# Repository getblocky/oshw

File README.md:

# oshw
Open source hardware designs for Blocky.

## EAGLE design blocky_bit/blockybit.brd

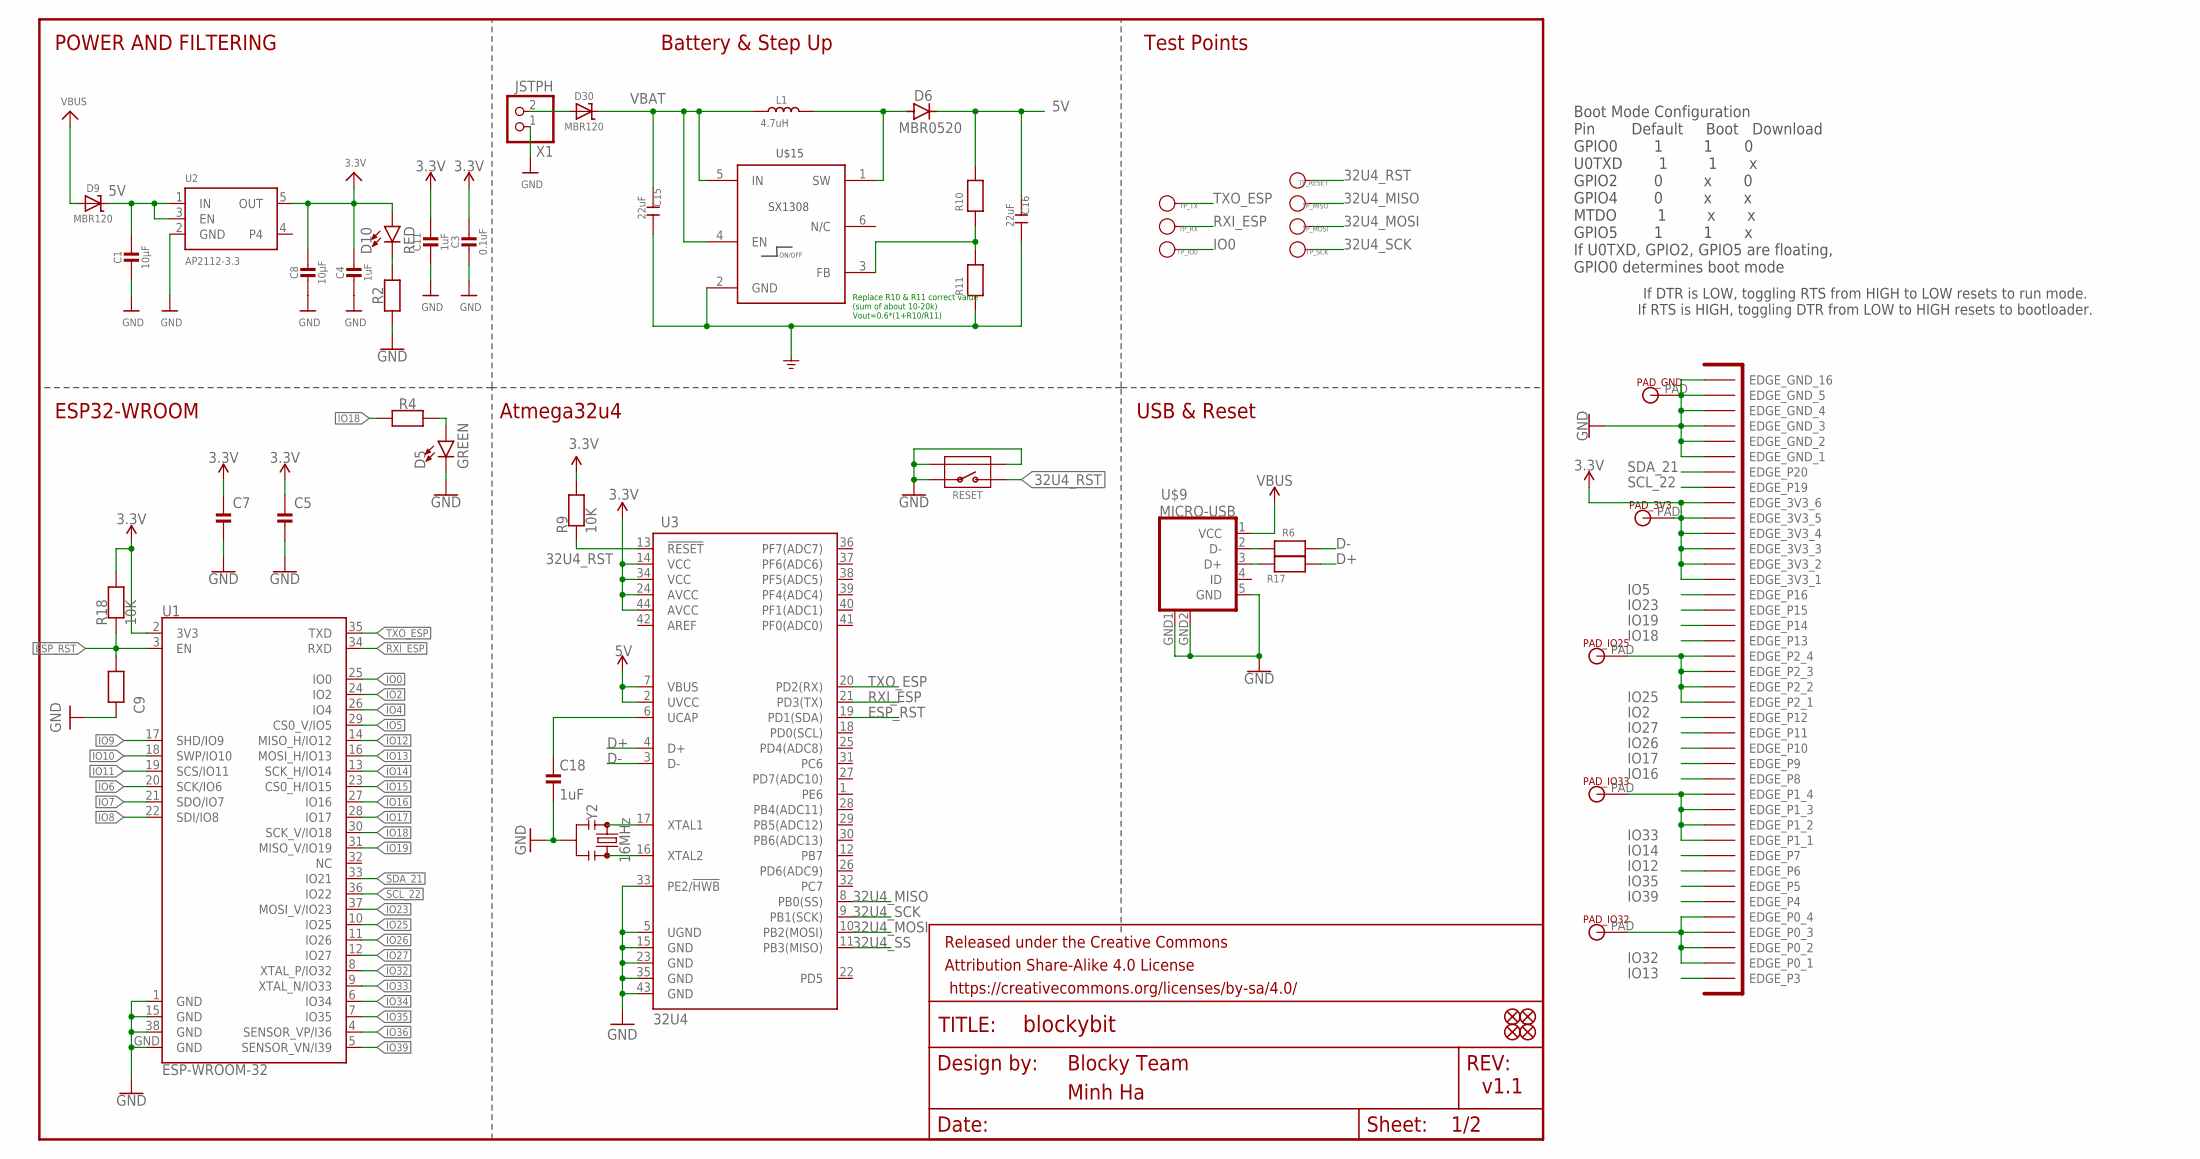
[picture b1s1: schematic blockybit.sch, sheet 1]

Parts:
C1, C8: 10µF; _0603
C3, C7, C9: 0.1uF; _0603
C4, C11, C18: 1uF; _0603
C5: 10uF; _0603
C15, C16: 22uF; C0805
D5: GREEN; LED-0603
D6: MBR0520; SOD123
D9, D30: MBR120; SOD-123
D10: RED; LED-0603
FD1, FD2, FD3, FD4: FIDUCIAL1X2; FIDUCIAL-1X2
FRAME1: FRAME-LETTERNO_PACKAGE; DUMMY
L1: 4.7uH; SD32-4R7MC
PAD_3V3: MICROBIT_PADMICROBIT_PAD_SMALL; MICROBIT_PAD_SMALL
PAD_GND: MICROBIT_PADMICROBIT_PAD_SMALL; MICROBIT_PAD_SMALL
PAD_IO25, PAD_IO32, PAD_IO33: MICROBIT_PADMICROBIT_PAD_SMALL; MICROBIT_PAD_SMALL
R2, R4: 1k; _0603
R6, R17: 22R; _0603
R9, R18: 10K; _0603
R10: 13K; _0603
R11: 2K; _0603
RESET: BUTTON-4P-REINFORCE'TS-1188E'; 4P-SMD-7X3.5X3.5H
TP_IO0: PAD-TEST-POINT'3535'; TP_3535
TP_MISO: PAD-TEST-POINT'3535'; TP_3535
TP_MOSI: PAD-TEST-POINT'3535'; TP_3535
TP_RESET: PAD-TEST-POINT'3535'; TP_3535
TP_RX: PAD-TEST-POINT'3535'; TP_3535
TP_SCK: PAD-TEST-POINT'3535'; TP_3535
TP_TX: PAD-TEST-POINT'3535'; TP_3535
U1: ESP-WROOM-32
U2: AP2112-3.3; SOT23-5
U3: 32U4; QFN-44
U$1: BBC_EDGE
U$9: MICRO-USB
U$15: SX1308; SOT-23-6
X1: JSTPH; JSTPH2
Y2: 16MHz; RESONATOR-SMD-3.2X1.3

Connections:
3.3V: C3.1, C4.1, C5.1, C7.1, C8.1, C11.1, D10.A, PAD_3V3.PAD, R9.2, R18.2, U1.2 (3V3), U2.5 (OUT), U3.14 (VCC), U3.24 (AVCC), U3.34 (VCC), U3.44 (AVCC), U$1.P$67 (EDGE_3V3_1), U$1.P$68 (EDGE_3V3_2), U$1.P$69 (EDGE_3V3_3), U$1.P$70 (EDGE_3V3_4), U$1.P$71 (EDGE_3V3_5), U$1.P$72 (EDGE_3V3_6); also elsewhere on the board
5V: C1.1, C16.1, D6.C, D9.C, R10.2, U2.1 (IN), U2.3 (EN), U3.2 (UVCC), U3.7 (VBUS); also elsewhere on the board
32U4_MISO: TP_MISO.T, U3.8 (PB0(SS))
32U4_MOSI: TP_MOSI.T, U3.10 (PB2(MOSI))
32U4_RST: R9.1, RESET.2, TP_RESET.T, U3.13 (!RESET)
32U4_SCK: TP_SCK.T, U3.9 (PB1(SCK))
32U4_SS: U3.11 (PB3(MISO))
D+: R17.1, U3.4 (D+)
D-: R6.1, U3.3 (D-)
ESP_RST: C9.1, R18.1, U1.3 (EN), U3.19 (PD1(SDA))
FB1: R10.1, R11.2, U$15.3 (FB)
GND: C1.2, C3.2, C4.2, C5.2, C7.2, C8.2, C9.2, C11.2, C15.2, C16.2, C18.1, D5.C, PAD_GND.PAD, R2.1, R11.1, RESET.1, RESET.S1, RESET.S2, U1.1 (GND), U1.15 (GND), U1.38 (GND), U1.GND, U2.2 (GND), U3.5 (UGND), U3.15 (GND), U3.23 (GND), U3.33 (PE2/!HWB), U3.35 (GND), U3.43 (GND), U$1.P$75 (EDGE_GND_1), U$1.P$76 (EDGE_GND_2), U$1.P$77 (EDGE_GND_3), U$1.P$78 (EDGE_GND_4), U$1.P$79 (EDGE_GND_5), U$1.P$80 (EDGE_GND_16), U$9.5 (GND), U$9.GND1 (GND), U$9.GND2 (GND), U$15.2 (GND), X1.1, Y2.2; also elsewhere on the board
IO0: TP_IO0.T, U1.25 (IO0)
IO2: U1.24 (IO2), U$1.P$58 (EDGE_P12)
IO4: U1.26 (IO4); also elsewhere on the board
IO5: U1.29 (CS0_V/IO5), U$1.P$66 (EDGE_P16)
IO6: U1.20 (SCK/IO6)
IO7: U1.21 (SDO/IO7)
IO8: U1.22 (SDI/IO8)
IO9: U1.17 (SHD/IO9)
IO10: U1.18 (SWP/IO10)
IO11: U1.19 (SCS/IO11)
IO12: U1.14 (MISO_H/IO12), U$1.P$48 (EDGE_P6)
IO13: U1.16 (MOSI_H/IO13), U$1.P$41 (EDGE_P3)
IO14: U1.13 (SCK_H/IO14), U$1.P$49 (EDGE_P7)
IO15: U1.23 (CS0_H/IO15)
IO16: U1.27 (IO16), U$1.P$54 (EDGE_P8)
IO17: U1.28 (IO17), U$1.P$55 (EDGE_P9)
IO18: R4.1, U1.30 (SCK_V/IO18), U$1.P$63 (EDGE_P13)
IO19: U1.31 (MISO_V/IO19), U$1.P$64 (EDGE_P14)
IO23: U1.37 (MOSI_V/IO23), U$1.P$65 (EDGE_P15)
IO25: PAD_IO25.PAD, U1.10 (IO25), U$1.P$59 (EDGE_P2_1), U$1.P$60 (EDGE_P2_2), U$1.P$61 (EDGE_P2_3), U$1.P$62 (EDGE_P2_4); also elsewhere on the board
IO26: U1.11 (IO26), U$1.P$56 (EDGE_P10)
IO27: U1.12 (IO27), U$1.P$57 (EDGE_P11); also elsewhere on the board
IO32: PAD_IO32.PAD, U1.8 (XTAL_P/IO32), U$1.P$42 (EDGE_P0_1), U$1.P$43 (EDGE_P0_2), U$1.P$44 (EDGE_P0_3), U$1.P$45 (EDGE_P0_4)
IO33: PAD_IO33.PAD, U1.9 (XTAL_N/IO33), U$1.P$50 (EDGE_P1_1), U$1.P$51 (EDGE_P1_2), U$1.P$52 (EDGE_P1_3), U$1.P$53 (EDGE_P1_4); also elsewhere on the board
IO34: U1.6 (IO34); also elsewhere on the board
IO35: U1.7 (IO35), U$1.P$47 (EDGE_P5); also elsewhere on the board
IO36: U1.4 (SENSOR_VP/I36); also elsewhere on the board
IO39: U1.5 (SENSOR_VN/I39), U$1.P$46 (EDGE_P4)
unnamed: D30.A, X1.2
unnamed: D5.A, R4.2
unnamed: D10.C, R2.2
unnamed: U3.16 (XTAL2), Y2.3
unnamed: R6.2, U$9.2 (D-)
unnamed: U3.17 (XTAL1), Y2.1
unnamed: R17.2, U$9.3 (D+)
RXI_ESP: TP_RX.T, U1.34 (RXD), U3.21 (PD3(TX))
SCL_22: U1.36 (IO22), U$1.P$73 (EDGE_P19); also elsewhere on the board
SDA_21: U1.33 (IO21), U$1.P$74 (EDGE_P20); also elsewhere on the board
SW1: D6.A, L1.2, U$15.1 (SW)
TXO_ESP: TP_TX.T, U1.35 (TXD), U3.20 (PD2(RX))
UCAP: C18.2, U3.6 (UCAP)
VBAT: C15.1, D30.C, L1.1, U$15.4 (EN), U$15.5 (IN)
VBUS: D9.A, U$9.1 (VCC)

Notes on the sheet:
Boot Mode Configuration Pin Default Boot Download GPIO0 1 1 0 U0TXD 1 1 x GPIO2 0 x 0 GPIO4 0 x x MTDO 1 x x GPIO5 1 1 x If U0TXD, GPIO2, GPIO5 are floating, GPIO0 determines boot mode
If DTR is LOW, toggling RTS from HIGH to LOW resets to run mode. If RTS is HIGH, toggling DTR from LOW to HIGH resets to bootloader.
POWER AND FILTERING
Battery & Step Up
ESP32-WROOM
Atmega32u4
Test Points
Blocky Team
v1.1
Minh Ha
Replace R10 & R11 correct value (sum of about 10-20k) Vout=0.6*(1+R10/R11)
USB & Reset

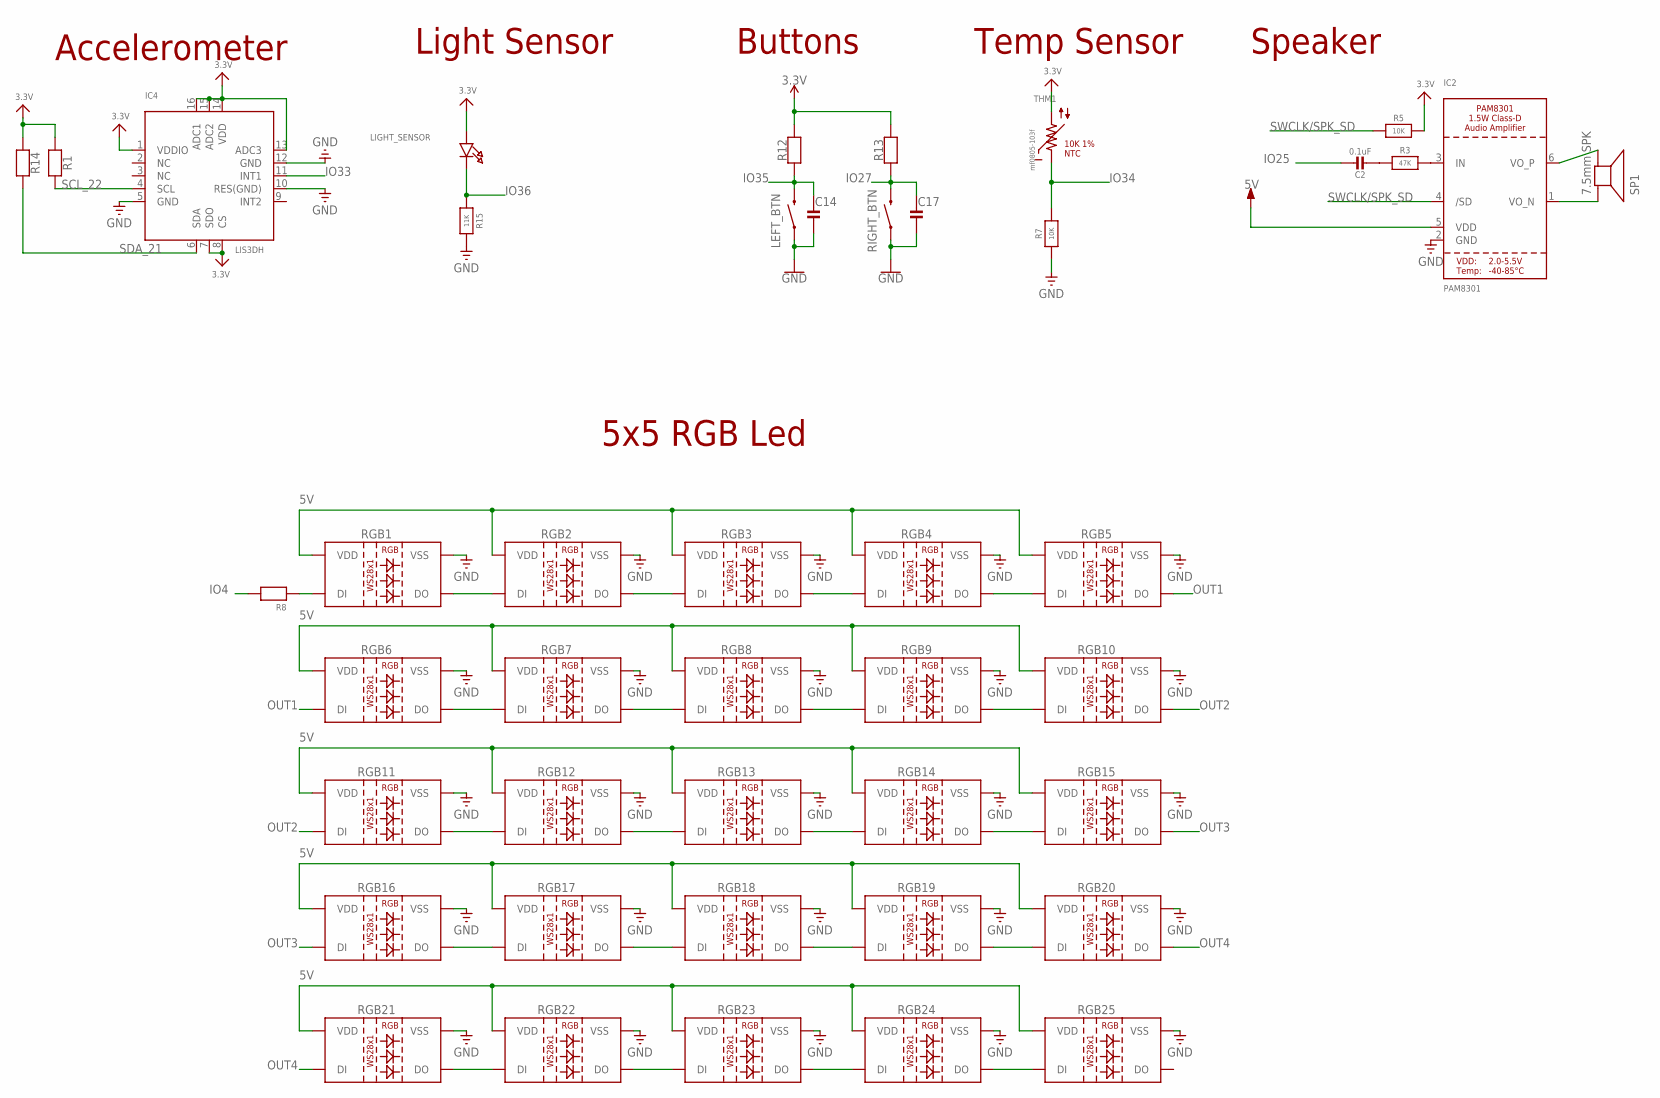
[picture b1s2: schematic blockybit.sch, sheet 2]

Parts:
C2: 0.1uF; _0603
C14, C17: 10pF; _0603
IC2: PAM8301; SOT23-6
IC4: LIS3DH; LGA16_3X3MM
LEFT_BTN: MOMENTARY-SWITCH-SPST-SMD-6.2MM-TALL; TACTILE_SWITCH_SMD_6.2MM_TALL
LIGHT_SENSOR: LED0805; CHIPLED_0805
R1, R5, R7, R12, R13, R14: 10K; _0603
R3: 47K; _0603
R8: 470; _0603
R15: 11K; _0603
RGB1, RGB2, RGB3, RGB4, RGB5, RGB6, RGB7, RGB8, RGB9, RGB10, RGB11, RGB12, RGB13, RGB14, RGB15, RGB16, RGB17, RGB18, RGB19, RGB20, RGB21, RGB22, RGB23, RGB24, RGB25: WS2812B; WS2812B-3535
RIGHT_BTN: MOMENTARY-SWITCH-SPST-SMD-6.2MM-TALL; TACTILE_SWITCH_SMD_6.2MM_TALL
SP1: 7.5mm SPK; BUZZER_SMT_7.5MM
THM1: mf0805-103f; R0805

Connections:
3.3V: IC4.1 (VDDIO), IC4.7 (SDO), IC4.8 (CS), IC4.13 (ADC3), IC4.14 (VDD), IC4.15 (ADC2), IC4.16 (ADC1), LIGHT_SENSOR.A, R1.1, R5.2, R12.2, R13.2, R14.1, THM1.2; also elsewhere on the board
5V: IC2.5 (VDD), RGB1.1 (VDD), RGB2.1 (VDD), RGB3.1 (VDD), RGB4.1 (VDD), RGB5.1 (VDD), RGB6.1 (VDD), RGB7.1 (VDD), RGB8.1 (VDD), RGB9.1 (VDD), RGB10.1 (VDD), RGB11.1 (VDD), RGB12.1 (VDD), RGB13.1 (VDD), RGB14.1 (VDD), RGB15.1 (VDD), RGB16.1 (VDD), RGB17.1 (VDD), RGB18.1 (VDD), RGB19.1 (VDD), RGB20.1 (VDD), RGB21.1 (VDD), RGB22.1 (VDD), RGB23.1 (VDD), RGB24.1 (VDD), RGB25.1 (VDD); also elsewhere on the board
GND: C14.2, C17.2, IC2.2 (GND), IC4.5 (GND), IC4.10 (RES(GND)), IC4.12 (GND), LEFT_BTN.A2 (1), R7.1, R15.1, RGB1.3 (VSS), RGB2.3 (VSS), RGB3.3 (VSS), RGB4.3 (VSS), RGB5.3 (VSS), RGB6.3 (VSS), RGB7.3 (VSS), RGB8.3 (VSS), RGB9.3 (VSS), RGB10.3 (VSS), RGB11.3 (VSS), RGB12.3 (VSS), RGB13.3 (VSS), RGB14.3 (VSS), RGB15.3 (VSS), RGB16.3 (VSS), RGB17.3 (VSS), RGB18.3 (VSS), RGB19.3 (VSS), RGB20.3 (VSS), RGB21.3 (VSS), RGB22.3 (VSS), RGB23.3 (VSS), RGB24.3 (VSS), RGB25.3 (VSS), RIGHT_BTN.A2 (1); also elsewhere on the board
IO4: R8.2; also elsewhere on the board
IO25: C2.1; also elsewhere on the board
IO27: C17.1, R13.1, RIGHT_BTN.B2 (2); also elsewhere on the board
IO33: IC4.11 (INT1); also elsewhere on the board
IO34: R7.2, THM1.1; also elsewhere on the board
IO35: C14.1, LEFT_BTN.B2 (2), R12.1; also elsewhere on the board
IO36: LIGHT_SENSOR.C, R15.2; also elsewhere on the board
unnamed: C2.2, R3.1
unnamed: IC2.3 (IN), R3.2
unnamed: IC2.6 (VO_P), SP1.-
unnamed: IC2.1 (VO_N), SP1.+
unnamed: RGB1.2 (DO), RGB2.4 (DI)
unnamed: RGB2.2 (DO), RGB3.4 (DI)
unnamed: RGB3.2 (DO), RGB4.4 (DI)
unnamed: RGB4.2 (DO), RGB5.4 (DI)
unnamed: RGB6.2 (DO), RGB7.4 (DI)
unnamed: RGB7.2 (DO), RGB8.4 (DI)
unnamed: R8.1, RGB1.4 (DI)
unnamed: RGB8.2 (DO), RGB9.4 (DI)
unnamed: RGB9.2 (DO), RGB10.4 (DI)
unnamed: RGB11.2 (DO), RGB12.4 (DI)
unnamed: RGB12.2 (DO), RGB13.4 (DI)
unnamed: RGB13.2 (DO), RGB14.4 (DI)
unnamed: RGB14.2 (DO), RGB15.4 (DI)
unnamed: RGB16.2 (DO), RGB17.4 (DI)
unnamed: RGB17.2 (DO), RGB18.4 (DI)
unnamed: RGB18.2 (DO), RGB19.4 (DI)
unnamed: RGB19.2 (DO), RGB20.4 (DI)
unnamed: RGB21.2 (DO), RGB22.4 (DI)
unnamed: RGB22.2 (DO), RGB23.4 (DI)
unnamed: RGB23.2 (DO), RGB24.4 (DI)
unnamed: RGB24.2 (DO), RGB25.4 (DI)
OUT1: RGB5.2 (DO), RGB6.4 (DI)
OUT2: RGB10.2 (DO), RGB11.4 (DI)
OUT3: RGB15.2 (DO), RGB16.4 (DI)
OUT4: RGB20.2 (DO), RGB21.4 (DI)
SCL_22: IC4.4 (SCL), R1.2; also elsewhere on the board
SDA_21: IC4.6 (SDA), R14.2; also elsewhere on the board
SWCLK/SPK_SD: IC2.4 (/SD), R5.1

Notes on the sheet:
Accelerometer
Light Sensor
Buttons
10K 1% NTC
Temp Sensor
Speaker
5x5 RGB Led

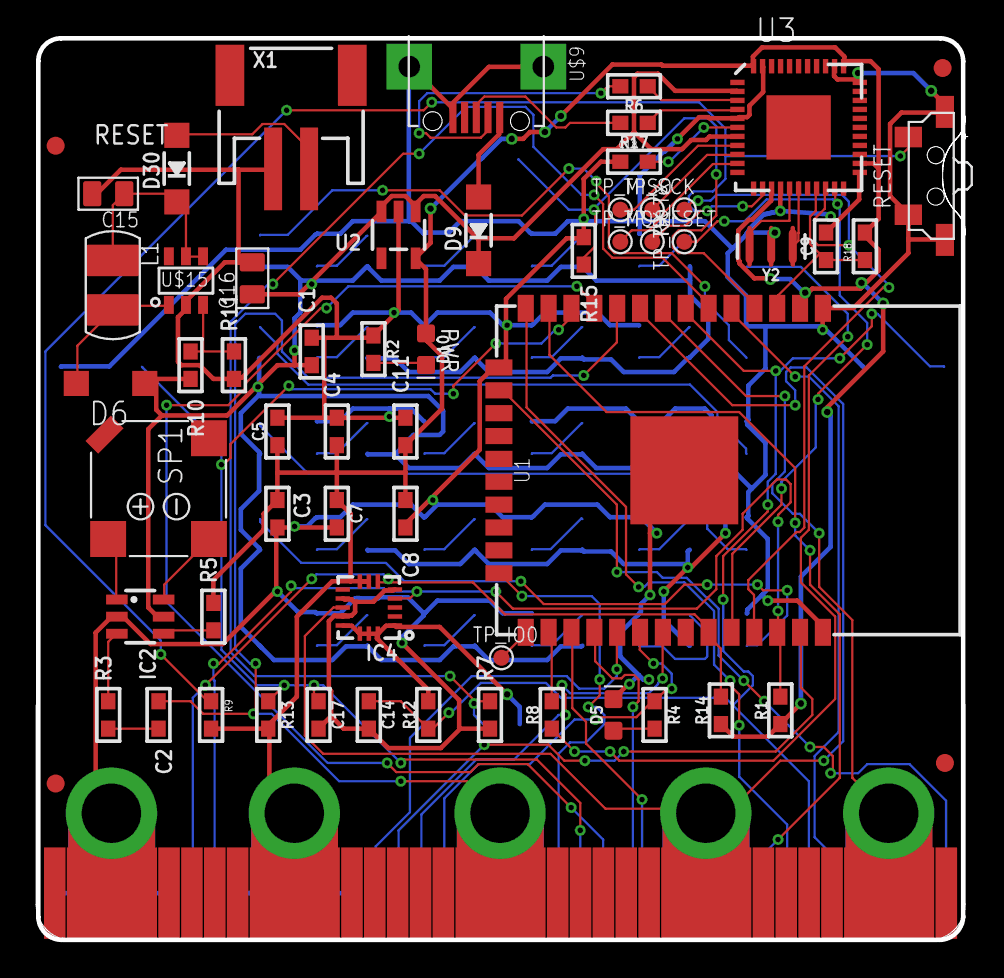
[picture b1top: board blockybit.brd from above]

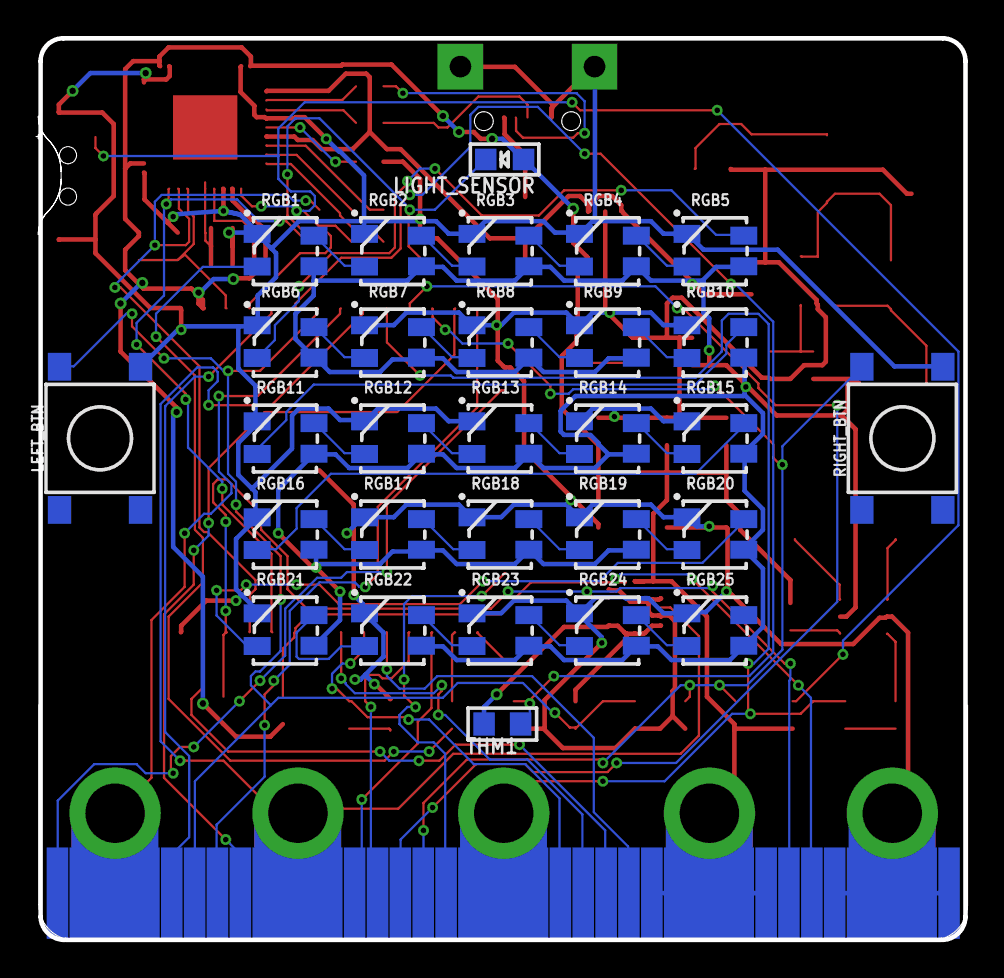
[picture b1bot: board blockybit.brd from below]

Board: 2 copper layers, 51.5 x 50.1 mm, 95 parts (29 on the bottom side), 77 nets.

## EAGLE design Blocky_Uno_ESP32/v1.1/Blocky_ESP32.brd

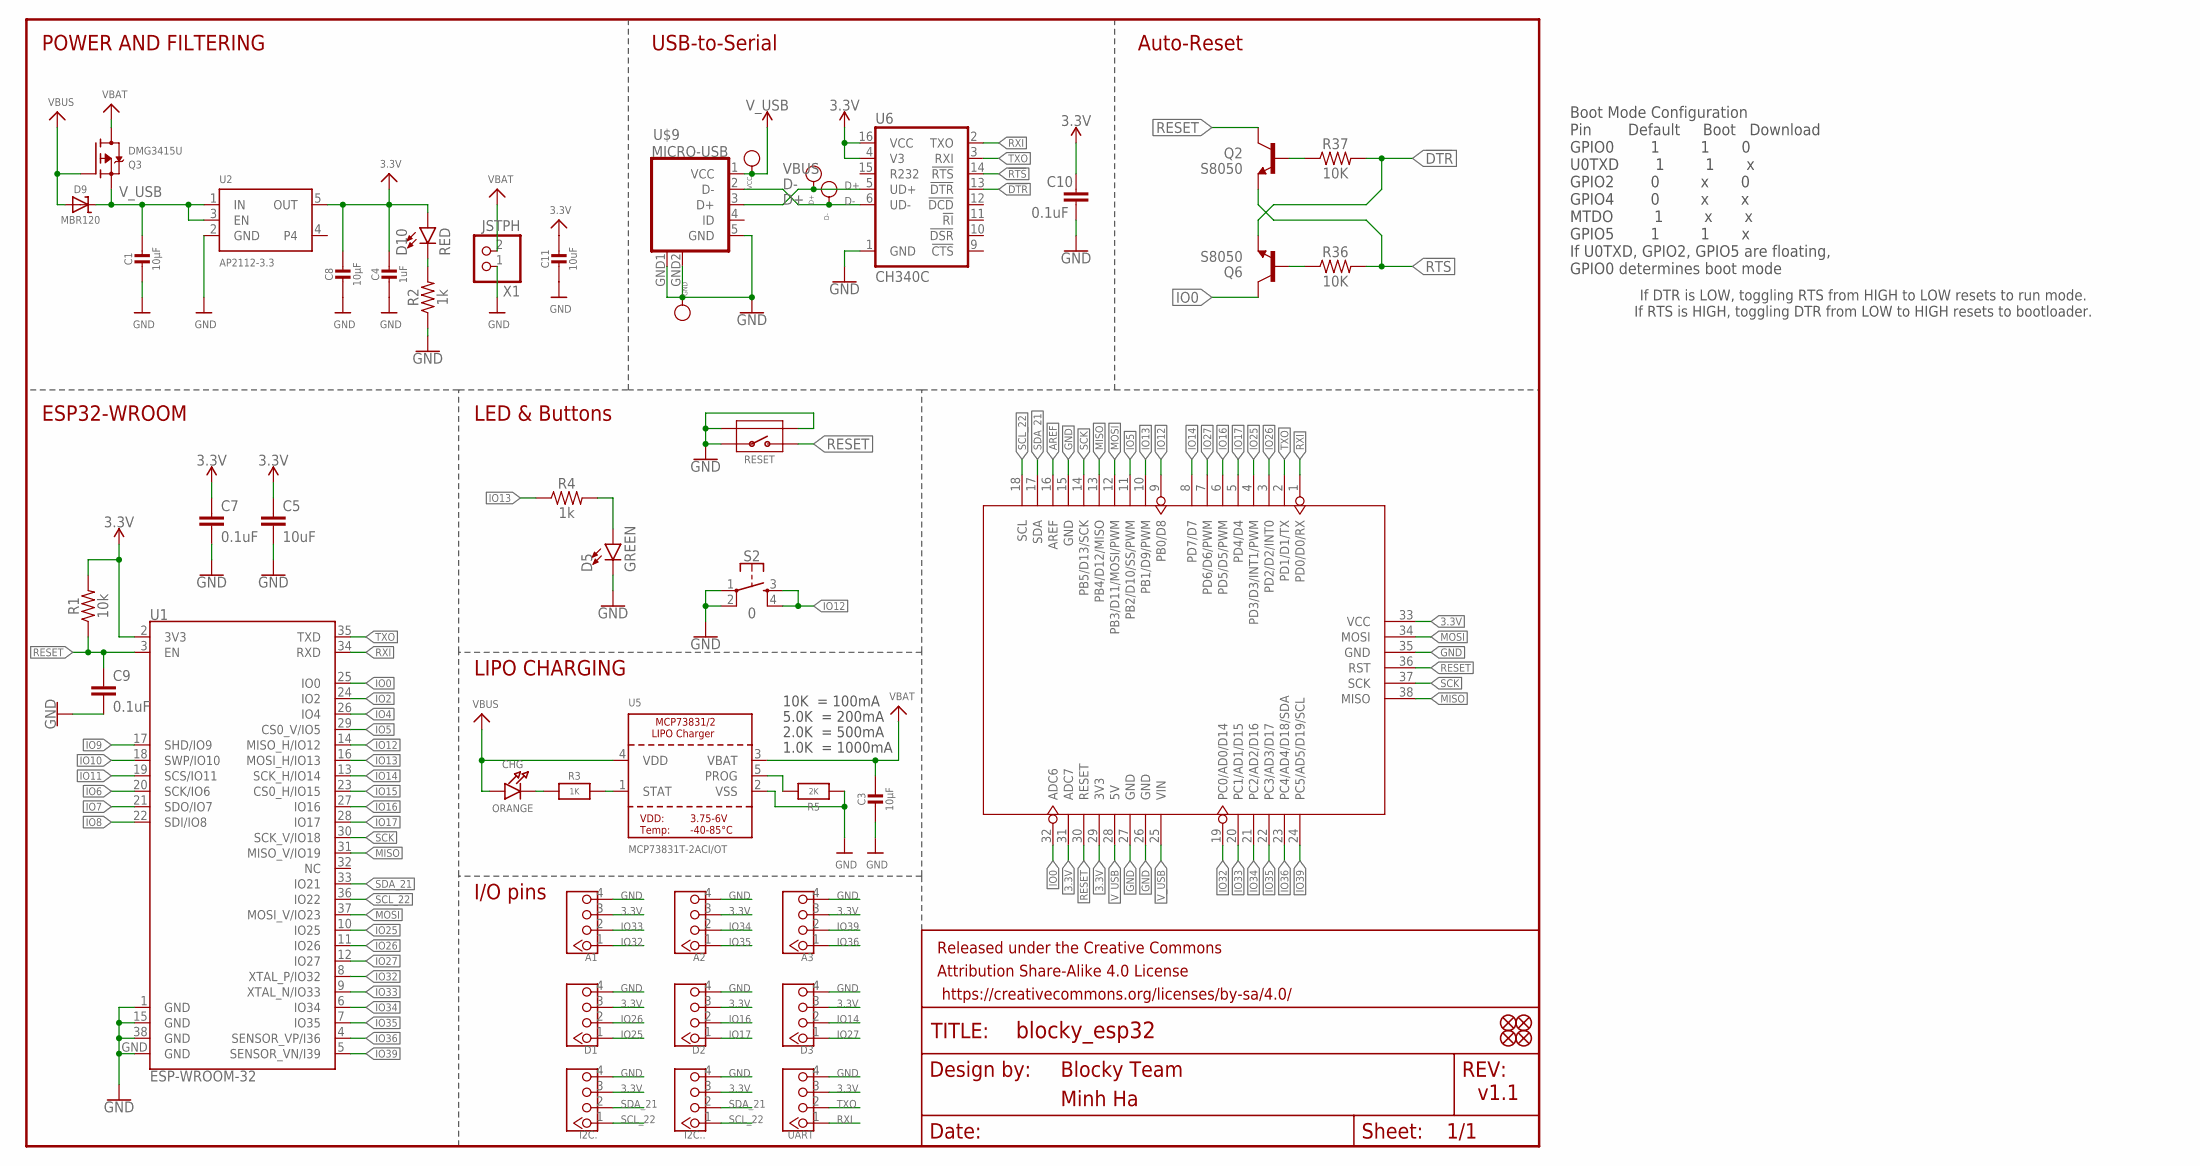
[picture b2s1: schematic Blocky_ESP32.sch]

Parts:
A1, A2, A3: TWIG-4P-2.0-2.0; 4P-2.0
C1, C3, C8: 10µF; _0603
C4: 1uF; _0603
C5: 10uF; 0603
C7, C9, C10: 0.1uF; 0603
C11: 10uF; _0603
CHG: ORANGE; CHIPLED_0603
D1, D2, D3: TWIG-4P-2.0-2.0; 4P-2.0
D5: GREEN; LED-0603
D9: MBR120; SOD-123
D10: RED; LED-0603
D+: PAD-TEST-POINT'4545'; TP_4545
D-: PAD-TEST-POINT'4545'; TP_4545
FD1, FD2, FD3, FD4: FIDUCIAL1X2; FIDUCIAL-1X2
FRAME1: FRAME-LETTERNO_PACKAGE; DUMMY
GND: PAD-TEST-POINT'4545'; TP_4545
I2C., I2C..: TWIG-4P-2.0-2.0; 4P-2.0
Q2, Q6: S8050; SOT23-3
Q3: DMG3415U; SOT23-R
R1: 10k; 0603
R2, R4: 1k; 0603
R3: 1K; 0603-NO
R5: 2K; 0603-NO
R36, R37: 10K; 0603
RESET: BUTTON-4P-REINFORCE'TS-1188E'; 4P-SMD-7X3.5X3.5H
S2: 0; TACTILE_SWITCH_SMD_4.6X2.8MM
U1: ESP-WROOM-32
U2: AP2112-3.3; SOT23-5
U3: ARDUINO-38P
U5: MCP73831T-2ACI/OT; SOT23-5
U6: CH340C; SO016
U$9: MICRO-USB
UART: TWIG-4P-2.0-2.0; 4P-2.0
VCC: PAD-TEST-POINT'4545'; TP_4545
X1: JSTPH; JSTPH2

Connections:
3.3V: A1.3, A2.3, A3.3, C4.1, C5.1, C7.1, C8.1, C10.1, C11.1, D1.3, D2.3, D3.3, D10.A, I2C..3, I2C...3, R1.2, U1.2 (3V3), U2.5 (OUT), U3.29 (3V3), U3.31 (ADC7), U3.33 (VCC), U6.4 (V3), U6.16 (VCC), UART.3
!DTR: Q6.2 (E), R37.2, U6.13 (!DTR)
!RTS: Q2.2 (E), R36.2, U6.14 (!RTS)
AREF: U3.16 (AREF)
D+: D+.T, U6.5 (UD+), U$9.3 (D+)
D-: D-.T, U6.6 (UD-), U$9.2 (D-)
GND: A1.4, A2.4, A3.4, C1.2, C3.2, C4.2, C5.2, C7.2, C8.2, C9.2, C10.2, C11.2, D1.4, D2.4, D3.4, D5.C, GND.T, I2C..4, I2C...4, R2.1, R5.1, RESET.1, RESET.S1, RESET.S2, S2.1, S2.2, U1.1 (GND), U1.15 (GND), U1.38 (GND), U1.GND, U2.2 (GND), U3.15 (GND), U3.26 (GND), U3.27 (GND), U3.35 (GND), U5.2 (VSS), U6.1 (GND), U$9.5 (GND), U$9.GND1 (GND), U$9.GND2 (GND), UART.4, X1.1
IO0: Q6.3 (C), U1.25 (IO0), U3.32 (ADC6)
IO2: U1.24 (IO2)
IO4: U1.26 (IO4)
IO5: U1.29 (CS0_V/IO5), U3.11 (PB2/D10/SS/PWM)
IO6: U1.20 (SCK/IO6)
IO7: U1.21 (SDO/IO7)
IO8: U1.22 (SDI/IO8)
IO9: U1.17 (SHD/IO9)
IO10: U1.18 (SWP/IO10)
IO11: U1.19 (SCS/IO11)
IO12: S2.3, S2.4, U1.14 (MISO_H/IO12), U3.9 (PB0/D8)
IO13: R4.1, U1.16 (MOSI_H/IO13), U3.10 (PB1/D9/PWM)
IO14: D3.2, U1.13 (SCK_H/IO14), U3.8 (PD7/D7)
IO15: U1.23 (CS0_H/IO15)
IO16: D2.2, U1.27 (IO16), U3.6 (PD5/D5/PWM)
IO17: D2.1, U1.28 (IO17), U3.5 (PD4/D4)
IO25: D1.1, U1.10 (IO25), U3.4 (PD3/D3/INT1/PWM)
IO26: D1.2, U1.11 (IO26), U3.3 (PD2/D2/INT0)
IO27: D3.1, U1.12 (IO27), U3.7 (PD6/D6/PWM)
IO32: A1.1, U1.8 (XTAL_P/IO32), U3.19 (PC0/AD0/D14)
IO33: A1.2, U1.9 (XTAL_N/IO33), U3.20 (PC1/AD1/D15)
IO34: A2.2, U1.6 (IO34), U3.21 (PC2/AD2/D16)
IO35: A2.1, U1.7 (IO35), U3.22 (PC3/AD3/D17)
IO36: A3.1, U1.4 (SENSOR_VP/I36), U3.23 (PC4/AD4/D18/SDA)
IO39: A3.2, U1.5 (SENSOR_VN/I39), U3.24 (PC5/AD5/D19/SCL)
MISO: U1.31 (MISO_V/IO19), U3.13 (PB4/D12/MISO), U3.38 (MISO)
MOSI: U1.37 (MOSI_V/IO23), U3.12 (PB3/D11/MOSI/PWM), U3.34 (MOSI)
unnamed: CHG.C, R3.1
unnamed: D5.A, R4.2
unnamed: Q2.1 (B), R37.1
unnamed: D10.C, R2.2
unnamed: Q6.1 (B), R36.1
PROG: R5.2, U5.5 (PROG)
RESET: C9.1, Q2.3 (C), R1.1, RESET.2, U1.3 (EN), U3.30 (RESET), U3.36 (RST)
RXI: U1.34 (RXD), U3.1 (PD0/D0/RX), U6.2 (TXO), UART.1
SCK: U1.30 (SCK_V/IO18), U3.14 (PB5/D13/SCK), U3.37 (SCK)
SCL_22: I2C..1, I2C...1, U1.36 (IO22), U3.18 (SCL)
SDA_21: I2C..2, I2C...2, U1.33 (IO21), U3.17 (SDA)
STAT: R3.2, U5.1 (STAT)
TXO: U1.35 (TXD), U3.2 (PD1/D1/TX), U6.3 (RXI), UART.2
VBAT: C3.1, Q3.3 (D), U5.3 (VBAT), X1.2
VBUS: CHG.A, D9.A, Q3.1 (G), U5.4 (VDD), U$9.1 (VCC), VCC.T
V_USB: C1.1, D9.C, Q3.2 (S), U2.1 (IN), U2.3 (EN), U3.25 (VIN), U3.28 (5V)

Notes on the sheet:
Boot Mode Configuration Pin Default Boot Download GPIO0 1 1 0 U0TXD 1 1 x GPIO2 0 x 0 GPIO4 0 x x MTDO 1 x x GPIO5 1 1 x If U0TXD, GPIO2, GPIO5 are floating, GPIO0 determines boot mode
If DTR is LOW, toggling RTS from HIGH to LOW resets to run mode. If RTS is HIGH, toggling DTR from LOW to HIGH resets to bootloader.
POWER AND FILTERING
USB-to-Serial
I/O pins
ESP32-WROOM
LED & Buttons
Auto-Reset
LIPO CHARGING
Blocky Team
v1.1
Minh Ha
10K = 100mA
5.0K = 200mA
2.0K = 500mA
1.0K = 1000mA

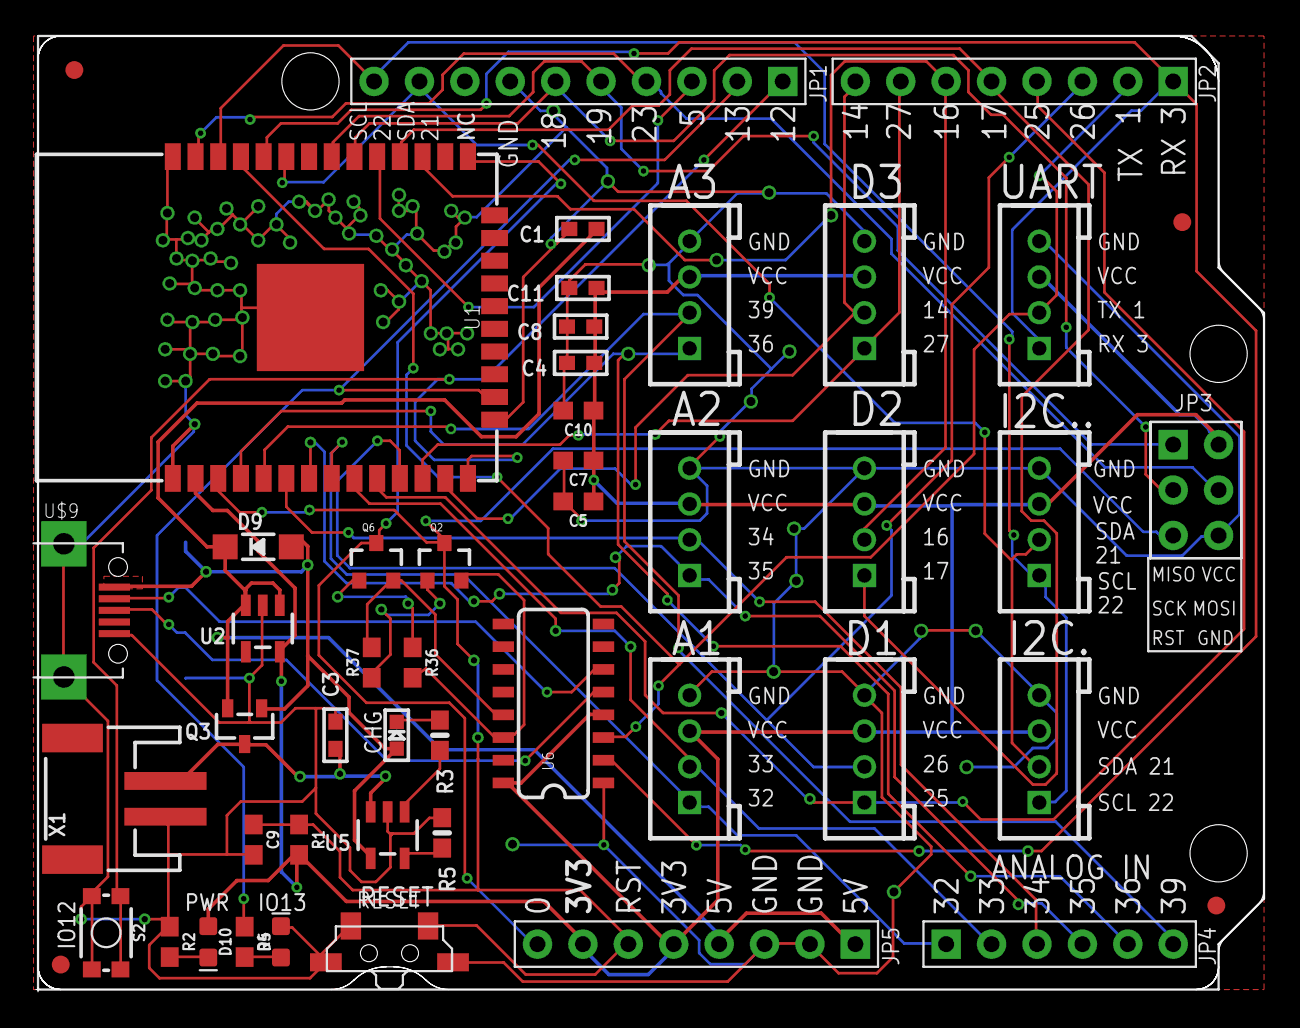
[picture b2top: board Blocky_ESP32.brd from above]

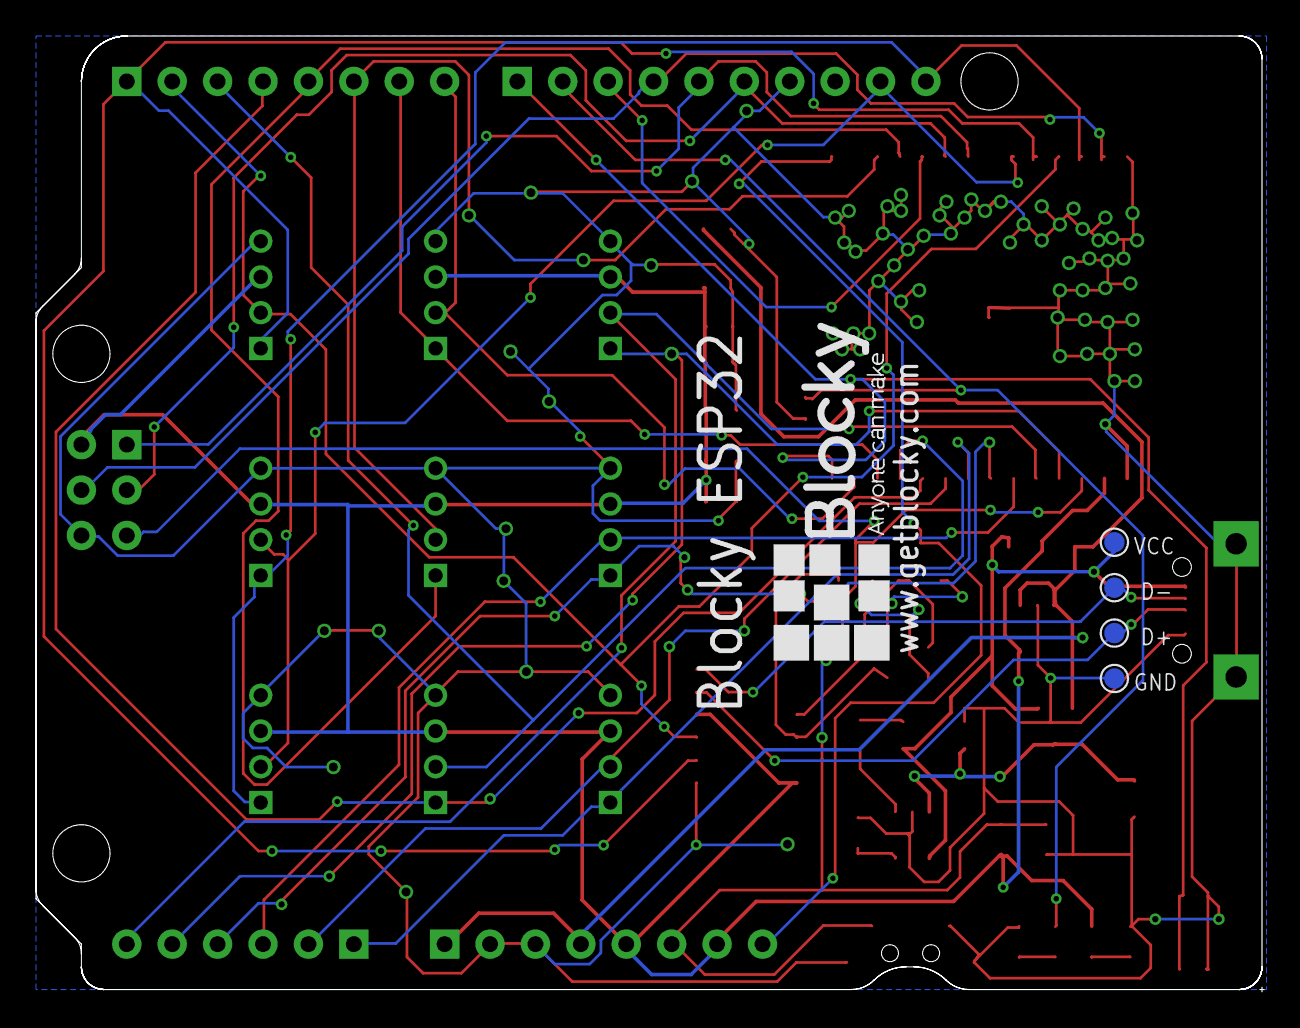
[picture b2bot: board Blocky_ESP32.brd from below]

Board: 2 copper layers, 68.7 x 53.5 mm, 51 parts (5 on the bottom side), 40 nets.

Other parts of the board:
U$4: BLOCKY_LOGO

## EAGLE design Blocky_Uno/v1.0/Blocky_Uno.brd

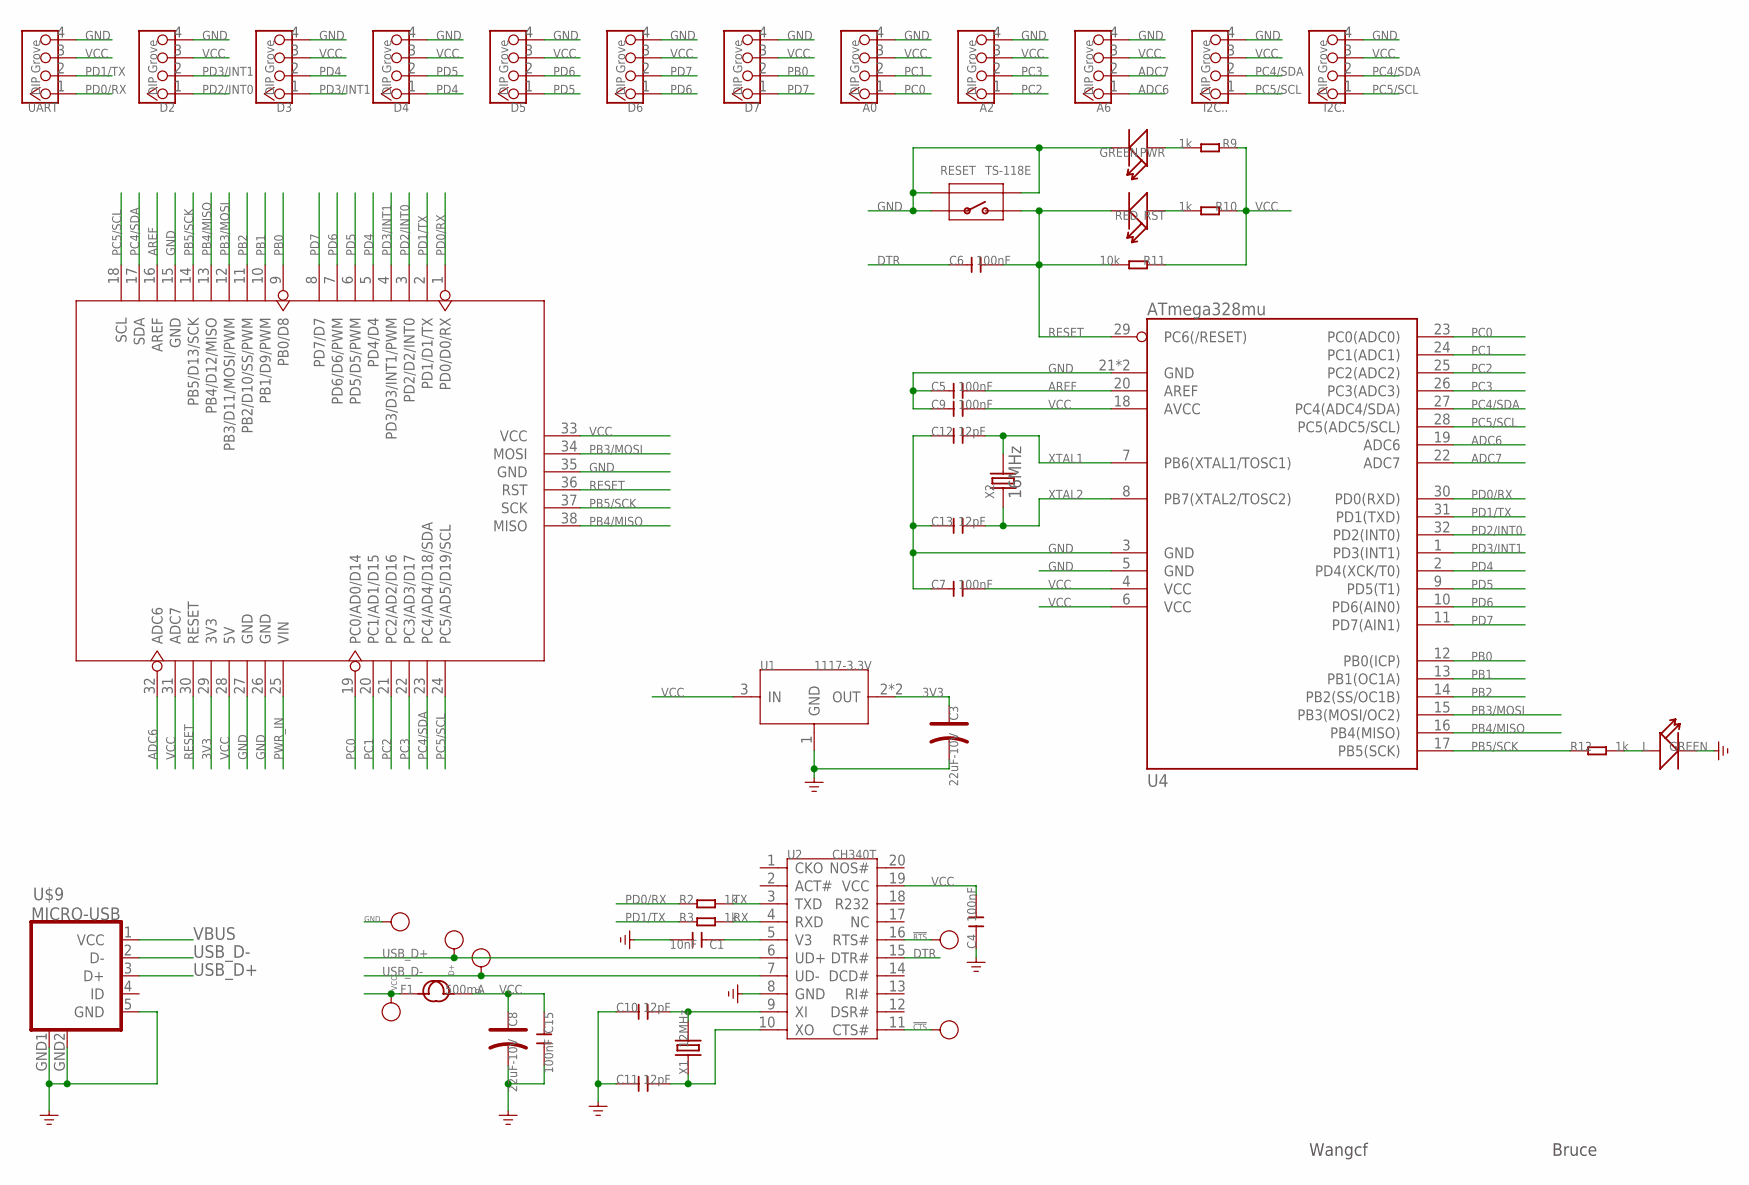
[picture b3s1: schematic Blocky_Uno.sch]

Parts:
!CTS: PAD-TEST-POINT'4545'; TP_4545
!RTS: PAD-TEST-POINT'4545'; TP_4545
A0, A2, A6: DIP Grove; 4P-2.0
C1: 10nF; C0603
C3, C8: 22uF-10V; AVX-A
C4, C5, C6, C7, C9, C15: 100nF; C0603
C10, C11, C12, C13: 12pF; C0603
D2, D3, D4, D5, D6, D7: DIP Grove; 4P-2.0
D+: PAD-TEST-POINT'4545'; TP_4545
D-: PAD-TEST-POINT'4545'; TP_4545
F1: 500mA; F1206
GND: PAD-TEST-POINT'4545'; TP_4545
I2C., I2C..: DIP Grove; 4P-2.0
L: GREEN; LED-0603
PWR: GREEN; LED-0603
R2, R3, R9, R10, R12: 1k; R0603
R11: 10k; R0603
RESET: TS-118E; 4P-SMD-7X3.5X3.5H
RST: RED; LED-0603
U1: 1117-3.3V; SOT89
U2: CH340T; SSOP20
U3: ARDUINO-38P
U4: ATmega328mu; MLF32X-W/HEAT
U$9: MICRO-USB
UART: DIP Grove; 4P-2.0
VCC: PAD-TEST-POINT'4545'; TP_4545
X1: 12MHz; 2P-SMD-5X3.2
X2: 16MHz; 2P-SMD-5X3.2

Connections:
3V3: C3.+, U1.2 (OUT), U1.4 (OUT), U3.29 (3V3)
ADC6: A6.1, U3.32 (ADC6), U4.19 (ADC6)
ADC7: A6.2, U4.22 (ADC7)
AREF: C5.2, U3.16 (AREF), U4.20 (AREF)
CTS: !CTS.T, U2.11 (CTS#)
DTR: C6.1, U2.15 (DTR#)
GND: A0.4, A2.4, A6.4, C1.2, C3.-, C4.1, C5.1, C7.1, C8.-, C9.1, C10.1, C11.1, C12.1, C13.1, C15.2, D2.4, D3.4, D4.4, D5.4, D6.4, D7.4, GND.T, I2C..4, I2C...4, L.-, PWR.-, RESET.1, RESET.S1, RESET.S2, U1.1 (GND), U2.8 (GND), U3.15 (GND), U3.26 (GND), U3.27 (GND), U3.35 (GND), U4.3 (GND), U4.5 (GND), U4.21 (GND), U4.HEAT (GND), U$9.5 (GND), U$9.GND1 (GND), U$9.GND2 (GND), UART.4
unnamed: R10.2, RST.+
unnamed: PWR.+, R9.2
unnamed: C10.2, U2.9 (XI), X1.2
unnamed: C11.2, U2.10 (XO), X1.1
unnamed: !RTS.T, U2.16 (RTS#)
unnamed: L.+, R12.2
PB0: D7.2, U3.9 (PB0/D8), U4.12 (PB0(ICP))
PB1: U3.10 (PB1/D9/PWM), U4.13 (PB1(OC1A))
PB2: U3.11 (PB2/D10/SS/PWM), U4.14 (PB2(SS/OC1B))
PB3/MOSI: U3.12 (PB3/D11/MOSI/PWM), U3.34 (MOSI), U4.15 (PB3(MOSI/OC2))
PB4/MISO: U3.13 (PB4/D12/MISO), U3.38 (MISO), U4.16 (PB4(MISO))
PB5/SCK: R12.1, U3.14 (PB5/D13/SCK), U3.37 (SCK), U4.17 (PB5(SCK))
PC0: A0.1, U3.19 (PC0/AD0/D14), U4.23 (PC0(ADC0))
PC1: A0.2, U3.20 (PC1/AD1/D15), U4.24 (PC1(ADC1))
PC2: A2.1, U3.21 (PC2/AD2/D16), U4.25 (PC2(ADC2))
PC3: A2.2, U3.22 (PC3/AD3/D17), U4.26 (PC3(ADC3))
PC4/SDA: I2C..2, I2C...2, U3.17 (SDA), U3.23 (PC4/AD4/D18/SDA), U4.27 (PC4(ADC4/SDA))
PC5/SCL: I2C..1, I2C...1, U3.18 (SCL), U3.24 (PC5/AD5/D19/SCL), U4.28 (PC5(ADC5/SCL))
PD0/RX: R2.1, U3.1 (PD0/D0/RX), U4.30 (PD0(RXD)), UART.1
PD1/TX: R3.1, U3.2 (PD1/D1/TX), U4.31 (PD1(TXD)), UART.2
PD2/INT0: D2.1, U3.3 (PD2/D2/INT0), U4.32 (PD2(INT0))
PD3/INT1: D2.2, D3.1, U3.4 (PD3/D3/INT1/PWM), U4.1 (PD3(INT1))
PD4: D3.2, D4.1, U3.5 (PD4/D4), U4.2 (PD4(XCK/T0))
PD5: D4.2, D5.1, U3.6 (PD5/D5/PWM), U4.9 (PD5(T1))
PD6: D5.2, D6.1, U3.7 (PD6/D6/PWM), U4.10 (PD6(AIN0))
PD7: D6.2, D7.1, U3.8 (PD7/D7), U4.11 (PD7(AIN1))
PWR_IN: U3.25 (VIN)
RESET: C6.2, R11.2, RESET.2, RST.-, U3.30 (RESET), U3.36 (RST), U4.29 (PC6(/RESET))
RX: R3.2, U2.4 (RXD)
TX: R2.2, U2.3 (TXD)
USB_D+: D+.T, U2.6 (UD+), U$9.3 (D+)
USB_D-: D-.T, U2.7 (UD-), U$9.2 (D-)
V3: C1.1, U2.5 (V3)
VBUS: F1.1, U$9.1 (VCC), VCC.T
VCC: A0.3, A2.3, A6.3, C4.2, C7.2, C8.+, C9.2, C15.1, D2.3, D3.3, D4.3, D5.3, D6.3, D7.3, F1.2, I2C..3, I2C...3, R9.1, R10.1, R11.1, U1.3 (IN), U2.19 (VCC), U3.28 (5V), U3.31 (ADC7), U3.33 (VCC), U4.4 (VCC), U4.6 (VCC), U4.18 (AVCC), UART.3
XTAL1: C12.2, U4.7 (PB6(XTAL1/TOSC1)), X2.2
XTAL2: C13.2, U4.8 (PB7(XTAL2/TOSC2)), X2.1

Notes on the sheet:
Wangcf
Bruce

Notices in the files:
parts and their libraries:
SparkFun-Connectors: Licensing: CC v3.0 Share-Alike You are welcome to use this library for commercial purposes.
SparkFun-PowerIC: Licensing: Creative Commons ShareAlike 4.0 International - https://creativecommons.org/licenses/by-sa/4.0
SparkFun-Aesthetics: Released under the Creative Commons
